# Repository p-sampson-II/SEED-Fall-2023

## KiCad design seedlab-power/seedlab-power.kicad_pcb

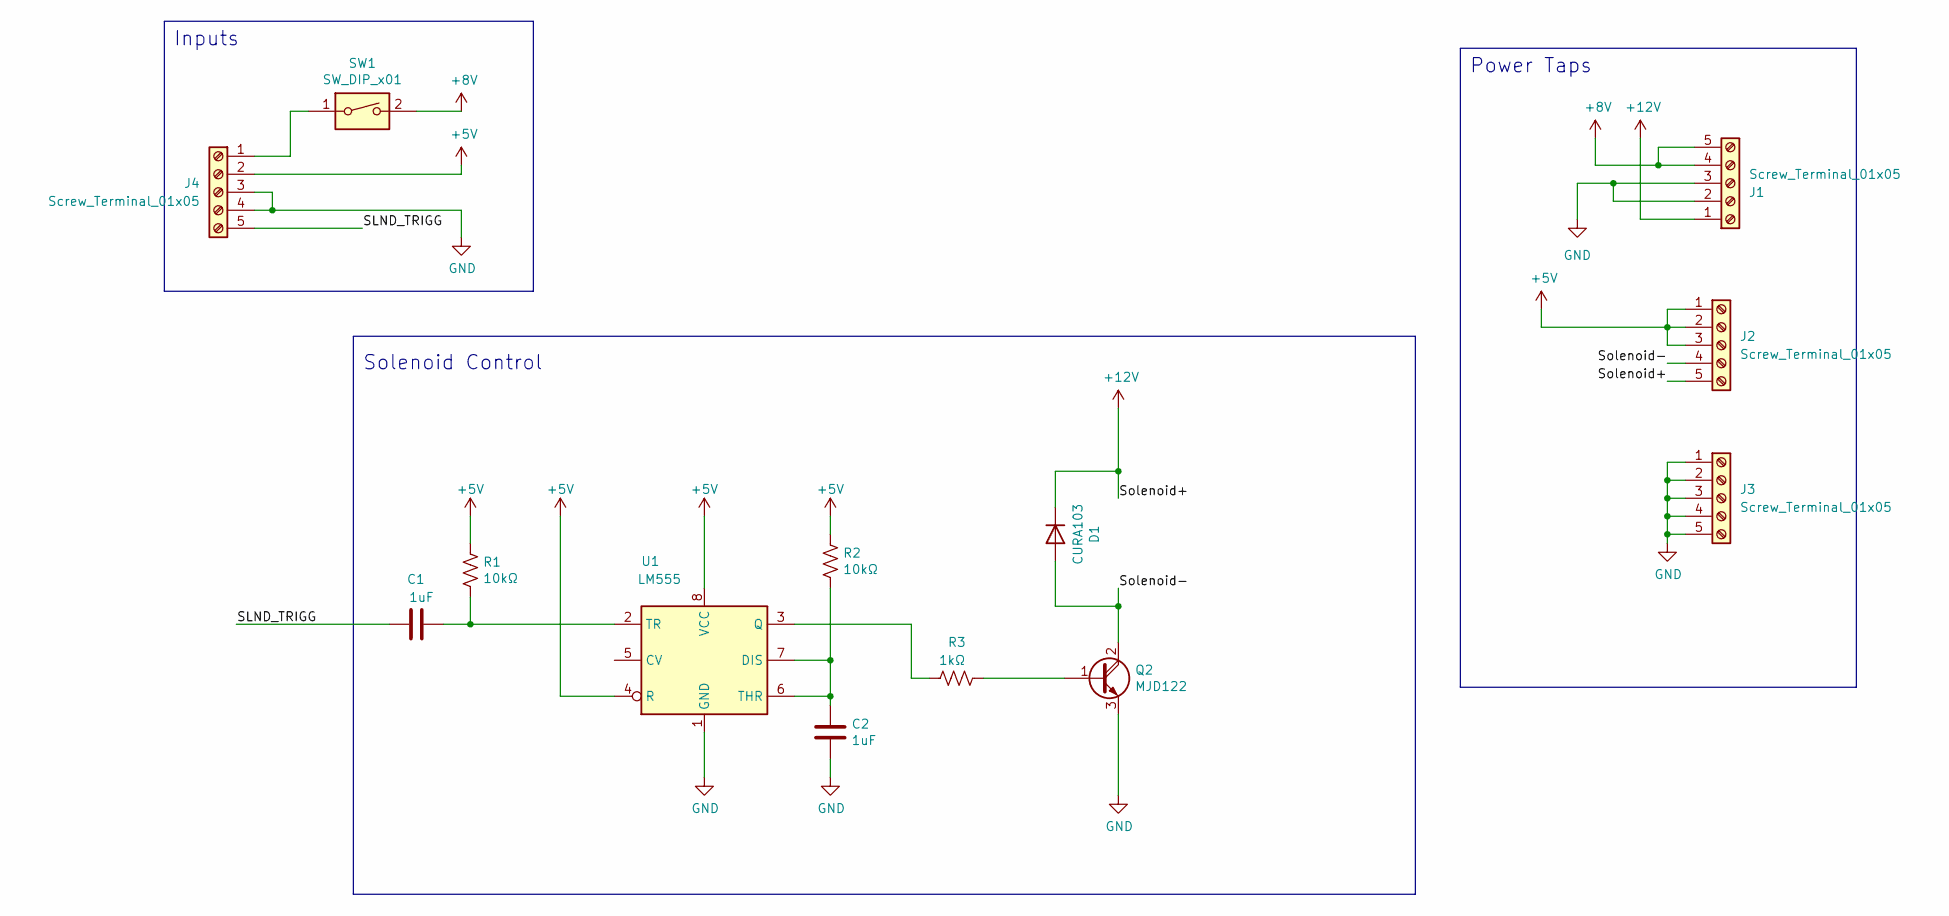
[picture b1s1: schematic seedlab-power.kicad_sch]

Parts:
C1, C2: 1uF; C_1206_3216Metric
D1: CURA103; DO-214AC
J1, J2, J3, J4: Screw_Terminal_01x05; TerminalBlock_Phoenix_PT-1,5-5-5.0-H_1x05_P5.00mm_Horizontal
Q2: MJD122; TO-263-2
R1, R2: 10kΩ; R_1206_3216Metric
R3: 1kΩ; R_1206_3216Metric
SW1: SW_DIP_x01; ANT11SF1CQE
U1: LM555; SOIC-8-1EP_3.9x4.9mm_P1.27mm_EP2.514x3.2mm

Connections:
+5V: J2.1, J2.2, J2.3, J4.2, R1.1, R2.1, U1.4 (R), U1.8 (VCC)
+8V: J1.4, J1.5, SW1.2
+12V: D1.1 (K), J1.1, J2.5
/SLND_TRIGG: C1.1, J4.5
/Solenoid-: D1.2 (A), J2.4, Q2.2 (C)
GND: C2.2, J1.2, J1.3, J3.1, J3.2, J3.3, J3.4, J3.5, J4.3, J4.4, Q2.3 (E), U1.1 (GND)
unnamed: J4.1, SW1.1
unnamed: Q2.1 (B), R3.1
unnamed: C2.1, R2.2, U1.6 (THR), U1.7 (DIS)
unnamed: R3.2, U1.3 (Q)
unnamed: C1.2, R1.2, U1.2 (TR)

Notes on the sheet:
Solenoid Control
Power Taps
Inputs

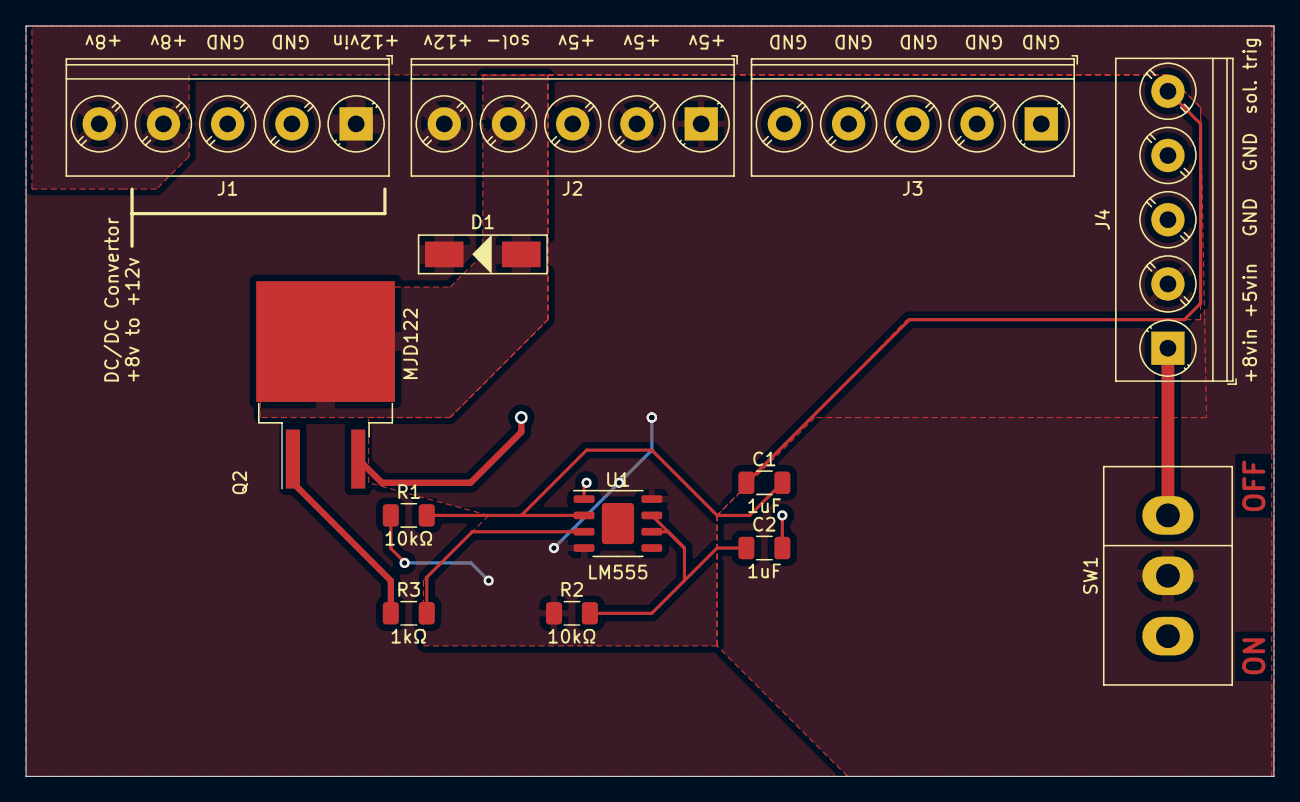
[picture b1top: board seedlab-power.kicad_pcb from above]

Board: 2 copper layers, 97.2 x 58.4 mm, 13 parts (0 on the bottom side), 11 nets.

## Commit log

2023-12-14 Added KiCad files
